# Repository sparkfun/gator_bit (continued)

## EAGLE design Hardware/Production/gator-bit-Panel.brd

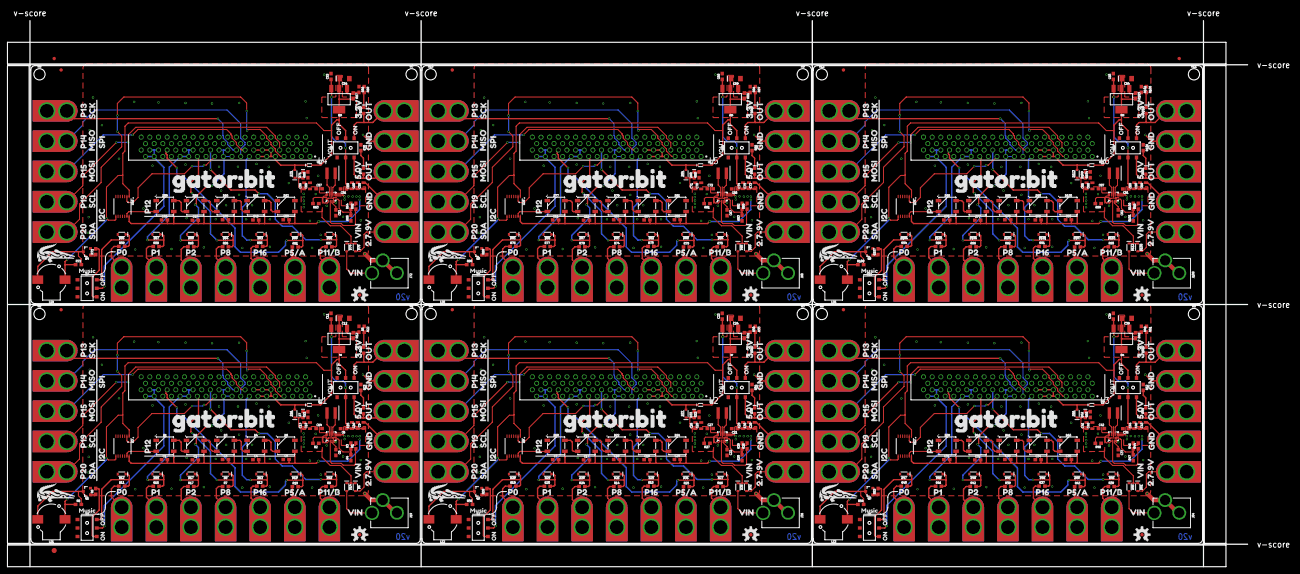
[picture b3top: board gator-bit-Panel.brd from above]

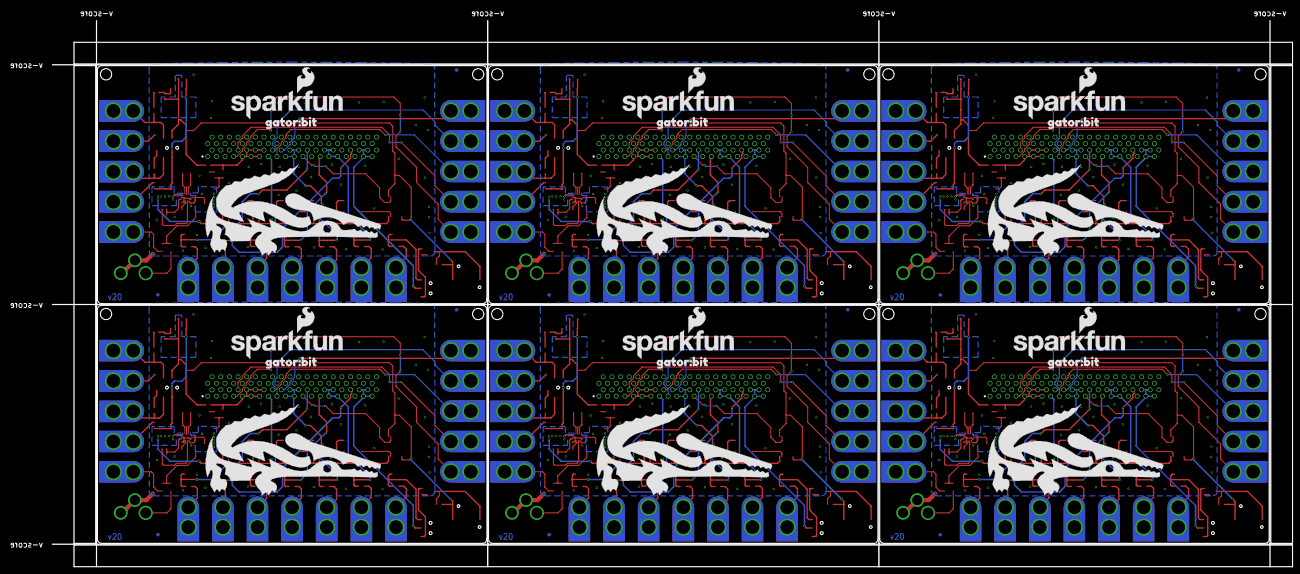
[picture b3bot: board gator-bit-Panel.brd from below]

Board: 2 copper layers, 364.0 x 160.3 mm, 765 parts (24 on the bottom side), 288 nets.

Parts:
C1, C2, C3, C4, C5, C7, C8, C11, C17, C18, C19, C20, C22, C23, C31, C32, C33, C34, C35, C37, C38, C46, C47, C48, C49, C50, C52, C53, C61, C62, C63, C64, C65, C67, C68, C76, C77, C78, C79, C80, C82, C83: 0.1uF; 0603
C6, C14, C21, C27, C36, C42, C51, C57, C66, C72, C81, C87: 10uF; 0603
C9, C15, C16, C28, C29, C30, C43, C44, C45, C58, C59, C60, C73, C74, C75, C88, C89, C90: 22uF; 0805
C10, C13, C25, C26, C40, C41, C55, C56, C70, C71, C85, C86: 10uF; 0805
C12, C24, C39, C54, C69, C84: 10uF; EIA3216
D1, D2, D3, D4, D5, D20, D21, D22, D23, D24, D39, D40, D41, D42, D43, D58, D59, D60, D61, D62, D77, D78, D79, D80, D81, D96, D97, D98, D99, D100: WS2812B
D6, D14, D16, D32, D36, D37, D51, D55, D56, D70, D74, D75, D89, D93, D94, D108, D112, D113: 1A/23V/620mV; SOD-323
D7, D9, D11, D33, D34, D35, D52, D53, D54, D71, D72, D73, D90, D91, D92, D109, D110, D111: RED; LED-0603
D8, D10, D12, D13, D15, D17, D19, D25, D26, D27, D28, D29, D30, D31, D44, D45, D46, D47, D48, D49, D50, D63, D64, D65, D66, D67, D68, D69, D82, D83, D84, D85, D86, D87, D88, D101, D102, D103, D104, D105, D106, D107: 3.6V; SOD-323
D18, D38, D57, D76, D95, D114: 120mA/40V/370mV; SOD-523
E$1, E$2: FIDUCIAL-1X2
E$3: FIDUCIAL-1.5X3
FD1, FD2, FD3, FD4, FD5, FD6, FD7, FD8, FD9, FD10, FD11, FD12, FD13, FD14, FD15, FD16, FD17, FD18, FD19, FD20, FD21, FD22, FD23, FD24: FIDUCIAL1X2; FIDUCIAL-1X2
FRAME1, FRAME2, FRAME3, FRAME4, FRAME5, FRAME6, FRAME7, FRAME8, FRAME9, FRAME10, FRAME11, FRAME12: FRAME-LETTER; CREATIVE_COMMONS
H1, H2, H3, H4, H5, H6, H7, H8, H9, H10, H11, H12: STAND-OFF
J1, J2, J3, J4, J5, J6, J7, J8, J9, J10, J11, J12, J13, J14, J15, J16, J17, J18, J20, J21, J22, J23, J24, J25, J26, J27, J28, J29, J30, J31, J32, J33, J34, J35, J37, J38, J39, J40, J41, J42, J43, J44, J45, J46, J47, J48, J49, J50, J51, J52, J53, J55, J56, J57, J58, J59, J60, J61, J62, J63, J64, J65, J66, J67, J68, J69, J70, J71, J73, J74, J75, J76, J77, J78, J79, J80, J81, J82, J83, J84, J85, J86, J87, J88, J89, J91, J92, J93, J94, J95, J96, J97, J98, J99, J100, J101, J102, J103, J104, J105, J106, J107: GATOR
J19, J36, J54, J72, J90, J108: POWER_JACKPTH_LOCK; POWER_JACK_PTH_LOCK
L1, L2, L3, L4, L5, L6: 1.5uH; XFL4020
LOGO1, LOGO4, LOGO7, LOGO10, LOGO13, LOGO16: SFE_LOGO_NAME_FLAME.3_INCH; SFE_LOGO_NAME_FLAME_.3
LOGO2, LOGO5, LOGO8, LOGO11, LOGO14, LOGO17: OSHW-LOGOM; OSHW-LOGO-M
LOGO3, LOGO6, LOGO9, LOGO12, LOGO15, LOGO18: REVISION
LS1, LS2, LS3, LS4, LS5, LS6: BUZZER-SMD; BUZZER-CCV
Q1, Q2, Q3, Q4, Q5, Q6: 600mA/40V; SOT23-3
R1, R4, R26, R29, R44, R47, R62, R65, R80, R83, R98, R101: 100k; 0603
R2, R27, R45, R63, R81, R99: 10.2K; 0603
R3, R28, R46, R64, R82, R100: 523k; 0603
R5, R30, R48, R66, R84, R102: 390; 0603
R6, R7, R9, R10, R11, R13, R14, R15, R16, R17, R18, R19, R20, R24, R25, R35, R37, R38, R39, R40, R41, R42, R43, R53, R55, R56, R57, R58, R59, R60, R61, R71, R73, R74, R75, R76, R77, R78, R79, R89, R91, R92, R93, R94, R95, R96, R97, R107: 100; 0603
R8, R36, R54, R72, R90, R108: 10k; 0603
R12, R31, R49, R67, R85, R103: 240; 0603
R21, R22, R23, R32, R33, R34, R50, R51, R52, R68, R69, R70, R86, R87, R88, R104, R105, R106: 1k; 0603
S1, S2, S3, S4, S5, S6, S7, S8, S9, S10, S11, S12: SWITCH_DPDT_SMD_AYZ0202
U1, U6, U10, U14, U18, U22: TPS63070; TPS63070RNM
U2, U5, U9, U13, U17, U21: micro:bit; MICRO:BIT_RA_PTH
U3, U8, U12, U16, U20, U24: TXB0104; TSSOP14
U4, U7, U11, U15, U19, U23: ADJ REG 1.5A; SOT223
U$1, U$4, U$75, U$112, U$149, U$186: 2#7#9V21
U$2, U$38, U$76, U$113, U$150, U$187: 3#3V25
U$3, U$40, U$77, U$114, U$151, U$188: 5#0V23
U$5, U$41, U$78, U$115, U$152, U$189: GATOR#BIT26
U$6, U$42, U$79, U$116, U$153, U$190: GATOR#BIT32
U$7, U$8, U$43, U$44, U$80, U$81, U$117, U$118, U$154, U$155, U$191, U$192: GND22
U$9, U$45, U$82, U$119, U$156, U$193: I2C7
U$10, U$46, U$83, U$120, U$157, U$194: MISO5
U$11, U$47, U$84, U$121, U$158, U$195: MOSI4
U$12, U$48, U$85, U$122, U$159, U$196: MUSIC28
U$13, U$36, U$49, U$72, U$86, U$109, U$123, U$146, U$160, U$183, U$197, U$220: OFF29
U$14, U$37, U$50, U$73, U$87, U$110, U$124, U$147, U$161, U$184, U$198, U$221: ON30
U$15, U$16, U$51, U$52, U$88, U$89, U$125, U$126, U$162, U$163, U$199, U$200: OUT24
U$17, U$53, U$90, U$127, U$164, U$201: P5#A18
U$18, U$54, U$91, U$128, U$165, U$202: P11#B19
U$19, U$55, U$92, U$129, U$166, U$203: P013
U$20, U$56, U$93, U$130, U$167, U$204: P114
U$21, U$57, U$94, U$131, U$168, U$205: P130
U$22, U$58, U$95, U$132, U$169, U$206: P199
U$23, U$59, U$96, U$133, U$170, U$207: P208
U$24, U$60, U$97, U$134, U$171, U$208: P215
U$25, U$61, U$98, U$135, U$172, U$209: P816
U$26, U$62, U$99, U$136, U$173, U$210: P1227
U$27, U$63, U$100, U$137, U$174, U$211: P1411
U$28, U$64, U$101, U$138, U$175, U$212: P1510
U$29, U$65, U$102, U$139, U$176, U$213: P1617
U$30, U$66, U$103, U$140, U$177, U$214: SCK1
U$31, U$67, U$104, U$141, U$178, U$215: SCL2
U$32, U$68, U$105, U$142, U$179, U$216: SDA3
U$33, U$69, U$106, U$143, U$180, U$217: SPI6
U$34, U$39, U$70, U$74, U$107, U$111, U$144, U$148, U$181, U$185, U$218, U$222: VIN20
U$35, U$71, U$108, U$145, U$182, U$219: VOUT31

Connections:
3.3V: C12.+, D18.A, LS1.+, R8.1, R12.2, S1.2, U3.1, U3.8, U4.2, U4.4
3.3V1: C24.+, D38.A, LS2.+, R31.2, R36.1, S4.2, U7.2, U7.4, U8.1, U8.8
3.3V2: C39.+, D57.A, LS3.+, R49.2, R54.1, S6.2, U11.2, U11.4, U12.1, U12.8
3.3V3: C54.+, D76.A, LS4.+, R67.2, R72.1, S8.2, U15.2, U15.4, U16.1, U16.8
3.3V4: C69.+, D95.A, LS5.+, R85.2, R90.1, S10.2, U19.2, U19.4, U20.1, U20.8
3.3V5: C84.+, D114.A, LS6.+, R103.2, R108.1, S12.2, U23.2, U23.4, U24.1, U24.8
5V: C1.2, C2.2, C3.2, C4.2, C5.2, C6.1, C9.1, C11.1, C15.1, C16.1, D1.1, D2.1, D3.1, D4.1, D5.1, R1.2, R3.2, S1.5, U1.P$7, U3.14, U4.3
5V1: C7.2, C17.2, C18.2, C19.2, C20.2, C21.1, C23.1, C28.1, C29.1, C30.1, D20.1, D21.1, D22.1, D23.1, D24.1, R26.2, R28.2, S4.5, U6.P$7, U7.3, U8.14
5V2: C31.2, C32.2, C33.2, C34.2, C35.2, C36.1, C38.1, C43.1, C44.1, C45.1, D39.1, D40.1, D41.1, D42.1, D43.1, R44.2, R46.2, S6.5, U10.P$7, U11.3, U12.14
5V3: C46.2, C47.2, C48.2, C49.2, C50.2, C51.1, C53.1, C58.1, C59.1, C60.1, D58.1, D59.1, D60.1, D61.1, D62.1, R62.2, R64.2, S8.5, U14.P$7, U15.3, U16.14
5V4: C61.2, C62.2, C63.2, C64.2, C65.2, C66.1, C68.1, C73.1, C74.1, C75.1, D77.1, D78.1, D79.1, D80.1, D81.1, R80.2, R82.2, S10.5, U18.P$7, U19.3, U20.14
5V5: C76.2, C77.2, C78.2, C79.2, C80.2, C81.1, C83.1, C88.1, C89.1, C90.1, D96.1, D97.1, D98.1, D99.1, D100.1, R98.2, R100.2, S12.5, U22.P$7, U23.3, U24.14
GND: C1.1, C2.1, C3.1, C4.1, C5.1, C6.2, C8.2, C9.2, C10.2, C11.2, C12.-, C13.2, C14.2, C15.2, C16.2, D1.3, D2.3, D3.3, D4.3, D5.3, D8.A, D10.A, D12.A, D13.A, D15.A, D17.A, D19.A, J2.P$1, J2.P$2, J4.P$1, J4.P$2, J19.GND, J19.GNDBREAK, Q1.2, R4.1, R5.1, R21.1, R22.1, R23.1, U1.P$4, U1.P$6, U1.P$10, U1.P$15, U2.A1, U2.A2, U2.A3, U2.A4, U2.A5, U2.A6, U3.7
GND1: C7.1, C17.1, C18.1, C19.1, C20.1, C21.2, C22.2, C23.2, C24.-, C25.2, C26.2, C27.2, C28.2, C29.2, C30.2, D20.3, D21.3, D22.3, D23.3, D24.3, D25.A, D26.A, D27.A, D28.A, D29.A, D30.A, D31.A, J32.P$1, J32.P$2, J34.P$1, J34.P$2, J36.GND, J36.GNDBREAK, Q2.2, R29.1, R30.1, R32.1, R33.1, R34.1, U5.A1, U5.A2, U5.A3, U5.A4, U5.A5, U5.A6, U6.P$4, U6.P$6, U6.P$10, U6.P$15, U8.7
GND2: C31.1, C32.1, C33.1, C34.1, C35.1, C36.2, C37.2, C38.2, C39.-, C40.2, C41.2, C42.2, C43.2, C44.2, C45.2, D39.3, D40.3, D41.3, D42.3, D43.3, D44.A, D45.A, D46.A, D47.A, D48.A, D49.A, D50.A, J50.P$1, J50.P$2, J52.P$1, J52.P$2, J54.GND, J54.GNDBREAK, Q3.2, R47.1, R48.1, R50.1, R51.1, R52.1, U9.A1, U9.A2, U9.A3, U9.A4, U9.A5, U9.A6, U10.P$4, U10.P$6, U10.P$10, U10.P$15, U12.7
GND3: C46.1, C47.1, C48.1, C49.1, C50.1, C51.2, C52.2, C53.2, C54.-, C55.2, C56.2, C57.2, C58.2, C59.2, C60.2, D58.3, D59.3, D60.3, D61.3, D62.3, D63.A, D64.A, D65.A, D66.A, D67.A, D68.A, D69.A, J68.P$1, J68.P$2, J70.P$1, J70.P$2, J72.GND, J72.GNDBREAK, Q4.2, R65.1, R66.1, R68.1, R69.1, R70.1, U13.A1, U13.A2, U13.A3, U13.A4, U13.A5, U13.A6, U14.P$4, U14.P$6, U14.P$10, U14.P$15, U16.7
GND4: C61.1, C62.1, C63.1, C64.1, C65.1, C66.2, C67.2, C68.2, C69.-, C70.2, C71.2, C72.2, C73.2, C74.2, C75.2, D77.3, D78.3, D79.3, D80.3, D81.3, D82.A, D83.A, D84.A, D85.A, D86.A, D87.A, D88.A, J86.P$1, J86.P$2, J88.P$1, J88.P$2, J90.GND, J90.GNDBREAK, Q5.2, R83.1, R84.1, R86.1, R87.1, R88.1, U17.A1, U17.A2, U17.A3, U17.A4, U17.A5, U17.A6, U18.P$4, U18.P$6, U18.P$10, U18.P$15, U20.7
GND5: C76.1, C77.1, C78.1, C79.1, C80.1, C81.2, C82.2, C83.2, C84.-, C85.2, C86.2, C87.2, C88.2, C89.2, C90.2, D96.3, D97.3, D98.3, D99.3, D100.3, D101.A, D102.A, D103.A, D104.A, D105.A, D106.A, D107.A, J104.P$1, J104.P$2, J106.P$1, J106.P$2, J108.GND, J108.GNDBREAK, Q6.2, R101.1, R102.1, R104.1, R105.1, R106.1, U21.A1, U21.A2, U21.A3, U21.A4, U21.A5, U21.A6, U22.P$4, U22.P$6, U22.P$10, U22.P$15, U24.7
MBIN: D16.A, D18.C, U2.A9, U2.A10, U2.A11, U2.A12, U2.A13, U2.A14
MBIN1: D37.A, D38.C, U5.A9, U5.A10, U5.A11, U5.A12, U5.A13, U5.A14
MBIN2: D56.A, D57.C, U9.A9, U9.A10, U9.A11, U9.A12, U9.A13, U9.A14
MBIN3: D75.A, D76.C, U13.A9, U13.A10, U13.A11, U13.A12, U13.A13, U13.A14
MBIN4: D94.A, D95.C, U17.A9, U17.A10, U17.A11, U17.A12, U17.A13, U17.A14
MBIN5: D113.A, D114.C, U21.A9, U21.A10, U21.A11, U21.A12, U21.A13, U21.A14
unnamed: D20.2, D21.4
unnamed: L1.P$1, U1.P$11
unnamed: LS1.-, Q1.3, R8.2
unnamed: D1.2, D2.4
unnamed: D2.2, D3.4
unnamed: D3.2, D4.4
unnamed: D4.2, D5.4
unnamed: L1.P$2, U1.P$9
unnamed: D7.C, R21.2
unnamed: D21.2, D22.4
unnamed: R3.1, R4.2, U1.P$5
unnamed: C8.1, U1.P$3
unnamed: R2.2, U1.P$1, U1.P$14
unnamed: R1.1, U1.P$2
unnamed: D22.2, D23.4
unnamed: R5.2, R12.1, U4.1
unnamed: D23.2, D24.4
unnamed: L2.P$1, U6.P$11
unnamed: L2.P$2, U6.P$9
unnamed: R6.2, S3.3
unnamed: R27.2, U6.P$1, U6.P$14
unnamed: D9.C, R22.2
unnamed: D11.C, R23.2
unnamed: Q1.1, R6.1
unnamed: C22.1, U6.P$3
unnamed: R28.1, R29.2, U6.P$5
unnamed: R26.1, U6.P$2
unnamed: R30.2, R31.1, U7.1
unnamed: D33.C, R32.2
unnamed: D34.C, R33.2
unnamed: D35.C, R34.2
unnamed: R35.2, S2.3
unnamed: Q2.1, R35.1
unnamed: LS2.-, Q2.3, R36.2
unnamed: D39.2, D40.4
unnamed: D40.2, D41.4
unnamed: D41.2, D42.4
unnamed: D42.2, D43.4
unnamed: L3.P$1, U10.P$11
unnamed: L3.P$2, U10.P$9
unnamed: R45.2, U10.P$1, U10.P$14
unnamed: C37.1, U10.P$3
unnamed: R46.1, R47.2, U10.P$5
unnamed: R44.1, U10.P$2
unnamed: R48.2, R49.1, U11.1
unnamed: D52.C, R50.2
unnamed: D53.C, R51.2
unnamed: D54.C, R52.2
unnamed: R53.2, S5.3
unnamed: Q3.1, R53.1
unnamed: LS3.-, Q3.3, R54.2
unnamed: D58.2, D59.4
unnamed: D59.2, D60.4
unnamed: D60.2, D61.4
unnamed: D61.2, D62.4
unnamed: L4.P$1, U14.P$11
unnamed: L4.P$2, U14.P$9
unnamed: R63.2, U14.P$1, U14.P$14
unnamed: C52.1, U14.P$3
unnamed: R64.1, R65.2, U14.P$5
unnamed: R62.1, U14.P$2
unnamed: R66.2, R67.1, U15.1
unnamed: D71.C, R68.2
unnamed: D72.C, R69.2
unnamed: D73.C, R70.2
unnamed: R71.2, S7.3
unnamed: Q4.1, R71.1
unnamed: LS4.-, Q4.3, R72.2
unnamed: D77.2, D78.4
unnamed: D78.2, D79.4
unnamed: D79.2, D80.4
unnamed: D80.2, D81.4
unnamed: L5.P$1, U18.P$11
unnamed: L5.P$2, U18.P$9
unnamed: R81.2, U18.P$1, U18.P$14
unnamed: C67.1, U18.P$3
unnamed: R82.1, R83.2, U18.P$5
unnamed: R80.1, U18.P$2
unnamed: R84.2, R85.1, U19.1
unnamed: D90.C, R86.2
unnamed: D91.C, R87.2
unnamed: D92.C, R88.2
unnamed: R89.2, S9.3
unnamed: Q5.1, R89.1
unnamed: LS5.-, Q5.3, R90.2
unnamed: D96.2, D97.4
unnamed: D97.2, D98.4
unnamed: D98.2, D99.4
unnamed: D99.2, D100.4
unnamed: L6.P$1, U22.P$11
unnamed: L6.P$2, U22.P$9
unnamed: R99.2, U22.P$1, U22.P$14
unnamed: C82.1, U22.P$3
unnamed: R100.1, R101.2, U22.P$5
unnamed: R98.1, U22.P$2
unnamed: R102.2, R103.1, U23.1
unnamed: D109.C, R104.2
unnamed: D110.C, R105.2
unnamed: D111.C, R106.2
unnamed: R107.2, S11.3
unnamed: Q6.1, R107.1
unnamed: LS6.-, Q6.3, R108.2
P0: S3.2, U2.A36, U2.A37, U2.A38, U2.A39
P0+: J7.P$1, J7.P$2, R11.1
P0+1: J20.P$1, J20.P$2, R18.1
P0+2: J38.P$1, J38.P$2, R40.1
P0+3: J56.P$1, J56.P$2, R58.1
P0+4: J74.P$1, J74.P$2, R76.1
P0+5: J92.P$1, J92.P$2, R94.1
P1: D15.C, R15.2, U2.A28, U2.A29, U2.A30, U2.A31
P1+: J8.P$1, J8.P$2, R15.1
P1+1: J21.P$1, J21.P$2, R20.1
P1+2: J39.P$1, J39.P$2, R41.1
P1+3: J57.P$1, J57.P$2, R59.1
P1+4: J75.P$1, J75.P$2, R77.1
P1+5: J93.P$1, J93.P$2, R95.1
P2: D17.C, R17.2, U2.A19, U2.A20, U2.A21, U2.A22
P2+: J9.P$1, J9.P$2, R17.1
P2+1: J22.P$1, J22.P$2, R24.1
P2+2: J40.P$1, J40.P$2, R42.1
P2+3: J58.P$1, J58.P$2, R60.1
P2+4: J76.P$1, J76.P$2, R78.1
P2+5: J94.P$1, J94.P$2, R96.1
P3: D27.C, R16.2, U5.A24
P4: D31.C, R25.2, U5.A34
P5: D19.C, R19.2, U2.A34
P5+: J10.P$1, J10.P$2, R19.1
P5+1: J23.P$1, J23.P$2, R25.1
P5+2: J41.P$1, J41.P$2, R43.1
P5+3: J59.P$1, J59.P$2, R61.1
P5+4: J77.P$1, J77.P$2, R79.1
P5+5: J95.P$1, J95.P$2, R97.1
P6: S2.2, U5.A36, U5.A37, U5.A38, U5.A39
P7: D29.C, R20.2, U5.A28, U5.A29, U5.A30, U5.A31
P8: D8.C, R7.2, U2.A27
P8+: J11.P$1, J11.P$2, R7.1
P8+1: J24.P$1, J24.P$2, R14.1
P8+2: J42.P$1, J42.P$2, R38.1
P8+3: J60.P$1, J60.P$2, R56.1
P8+4: J78.P$1, J78.P$2, R74.1
P8+5: J96.P$1, J96.P$2, R92.1
P9: D26.C, R14.2, U5.A27
P10: D20.4, U8.13
P11: D10.C, R9.2, U2.A24
P11+: J18.P$1, J18.P$2, R9.1
P11+1: J31.P$1, J31.P$2, R16.1
P11+2: J49.P$1, J49.P$2, R39.1
P11+3: J67.P$1, J67.P$2, R57.1
P11+4: J85.P$1, J85.P$2, R75.1
P11+5: J103.P$1, J103.P$2, R93.1
P12: D1.4, U3.13
P12LL: U2.A23, U3.2
P12LL1: U5.A23, U8.2
P12LL2: U9.A23, U12.2
P12LL3: U13.A23, U16.2
P12LL4: U17.A23, U20.2
P12LL5: U21.A23, U24.2
P13: J12.P$1, J12.P$2, U2.A18
P14: J13.P$1, J13.P$2, U2.A17
P15: J14.P$1, J14.P$2, U2.A16
P16: D13.C, R13.2, U2.A15
P16+: J15.P$1, J15.P$2, R13.1
P16+1: J28.P$1, J28.P$2, R10.1
P16+2: J46.P$1, J46.P$2, R37.1
P16+3: J64.P$1, J64.P$2, R55.1
P16+4: J82.P$1, J82.P$2, R73.1
P16+5: J100.P$1, J100.P$2, R91.1
P17: D30.C, R24.2, U5.A19, U5.A20, U5.A21, U5.A22
P18: J25.P$1, J25.P$2, U5.A18
P19: J16.P$1, J16.P$2, U2.A8
P20: J17.P$1, J17.P$2, U2.A7
P21: J26.P$1, J26.P$2, U5.A17
P22: J27.P$1, J27.P$2, U5.A16
P23: D25.C, R10.2, U5.A15
P24: J29.P$1, J29.P$2, U5.A8
P25: J30.P$1, J30.P$2, U5.A7
P26: D46.C, R39.2, U9.A24
P27: D50.C, R43.2, U9.A34
P28: S5.2, U9.A36, U9.A37, U9.A38, U9.A39
P29: D48.C, R41.2, U9.A28, U9.A29, U9.A30, U9.A31
P30: D45.C, R38.2, U9.A27
P31: D39.4, U12.13
P32: D49.C, R42.2, U9.A19, U9.A20, U9.A21, U9.A22
P33: J43.P$1, J43.P$2, U9.A18
P34: J44.P$1, J44.P$2, U9.A17
P35: J45.P$1, J45.P$2, U9.A16
P36: D44.C, R37.2, U9.A15
P37: J47.P$1, J47.P$2, U9.A8
P38: J48.P$1, J48.P$2, U9.A7
P39: D65.C, R57.2, U13.A24
P40: D69.C, R61.2, U13.A34
P41: S7.2, U13.A36, U13.A37, U13.A38, U13.A39
P42: D67.C, R59.2, U13.A28, U13.A29, U13.A30, U13.A31
P43: D64.C, R56.2, U13.A27
P44: D58.4, U16.13
P45: D68.C, R60.2, U13.A19, U13.A20, U13.A21, U13.A22
P46: J61.P$1, J61.P$2, U13.A18
P47: J62.P$1, J62.P$2, U13.A17
P48: J63.P$1, J63.P$2, U13.A16
P49: D63.C, R55.2, U13.A15
P50: J65.P$1, J65.P$2, U13.A8
P51: J66.P$1, J66.P$2, U13.A7
P52: D84.C, R75.2, U17.A24
P53: D88.C, R79.2, U17.A34
P54: S9.2, U17.A36, U17.A37, U17.A38, U17.A39
P55: D86.C, R77.2, U17.A28, U17.A29, U17.A30, U17.A31
P56: D83.C, R74.2, U17.A27
P57: D77.4, U20.13
P58: D87.C, R78.2, U17.A19, U17.A20, U17.A21, U17.A22
P59: J79.P$1, J79.P$2, U17.A18
P60: J80.P$1, J80.P$2, U17.A17
P61: J81.P$1, J81.P$2, U17.A16
P62: D82.C, R73.2, U17.A15
P63: J83.P$1, J83.P$2, U17.A8
P64: J84.P$1, J84.P$2, U17.A7
P65: D103.C, R93.2, U21.A24
P66: D107.C, R97.2, U21.A34
P67: S11.2, U21.A36, U21.A37, U21.A38, U21.A39
P68: D105.C, R95.2, U21.A28, U21.A29, U21.A30, U21.A31
P69: D102.C, R92.2, U21.A27
P70: D96.4, U24.13
P71: D106.C, R96.2, U21.A19, U21.A20, U21.A21, U21.A22
P72: J97.P$1, J97.P$2, U21.A18
P73: J98.P$1, J98.P$2, U21.A17
P74: J99.P$1, J99.P$2, U21.A16
P75: D101.C, R91.2, U21.A15
P76: J101.P$1, J101.P$2, U21.A8
P77: J102.P$1, J102.P$2, U21.A7
PD: D12.C, R11.2, S3.1
PD1: D28.C, R18.2, S2.1
PD2: D47.C, R40.2, S5.1
PD3: D66.C, R58.2, S7.1
PD4: D85.C, R76.2, S9.1
PD5: D104.C, R94.2, S11.1
VIN: C10.1, C13.1, C14.1, D6.C, D7.A, D14.C, D16.C, R2.1, U1.P$12
VIN1: C25.1, C26.1, C27.1, D32.C, D33.A, D36.C, D37.C, R27.1, U6.P$12
VIN2: C40.1, C41.1, C42.1, D51.C, D52.A, D55.C, D56.C, R45.1, U10.P$12
VIN3: C55.1, C56.1, C57.1, D70.C, D71.A, D74.C, D75.C, R63.1, U14.P$12
VIN4: C70.1, C71.1, C72.1, D89.C, D90.A, D93.C, D94.C, R81.1, U18.P$12
VIN5: C85.1, C86.1, C87.1, D108.C, D109.A, D112.C, D113.C, R99.1, U22.P$12
VIN_TAB: D6.A, J3.P$1, J3.P$2
VIN_TAB1: D32.A, J33.P$1, J33.P$2
VIN_TAB2: D51.A, J51.P$1, J51.P$2
VIN_TAB3: D70.A, J69.P$1, J69.P$2
VIN_TAB4: D89.A, J87.P$1, J87.P$2
VIN_TAB5: D108.A, J105.P$1, J105.P$2
VOUT3.1: D34.A, J5.P$1, J5.P$2, S4.3
VOUT3.2: D53.A, J37.P$1, J37.P$2, S6.3
VOUT3.3: D9.A, J6.P$1, J6.P$2, S1.3
VOUT3.4: D72.A, J55.P$1, J55.P$2, S8.3
VOUT3.5: D91.A, J73.P$1, J73.P$2, S10.3
VOUT3.6: D110.A, J91.P$1, J91.P$2, S12.3
VOUT5.0: D11.A, J1.P$1, J1.P$2, S1.6
VOUT5.1: D35.A, J35.P$1, J35.P$2, S4.6
VOUT5.2: D54.A, J53.P$1, J53.P$2, S6.6
VOUT5.3: D73.A, J71.P$1, J71.P$2, S8.6
VOUT5.4: D92.A, J89.P$1, J89.P$2, S10.6
VOUT5.5: D111.A, J107.P$1, J107.P$2, S12.6
V_BATT: D14.A, J19.PWR
V_BATT1: D36.A, J36.PWR
V_BATT2: D55.A, J54.PWR
V_BATT3: D74.A, J72.PWR
V_BATT4: D93.A, J90.PWR
V_BATT5: D112.A, J108.PWR

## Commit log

2017-09-15 Pulling board file from personal repo
2017-09-15 Updated Board File Silk
2017-09-18 Updating BRD and SCH files -fixed switch problem - isolate speaker and protected pin 0 line -Added silk labels to GPIO -Aesthetics on SCH
2017-09-18 Updated SILK on BRD file
2017-09-20 Added a battery connector
2017-09-21 Add JST battery connector
2017-09-26 Updated design
2017-09-26 adding bstop
2017-09-26 adding OSHW logo, VIN range note
2017-09-26 updating resistor values
2017-10-16 Updating file
2017-10-24 Updating Design Files
2017-10-27 updating brd file
2017-10-27 Added Inductor
2017-10-31 Updated Brd and Sch files
2017-11-03 added SOT223 package for 3.3V regulated output
2017-11-03 added holes for lego compatibility
2017-11-03 decreased size of 3.3V polygon pour
2017-11-06 Fixing traces
2017-11-06 Updated parts with SKUs
2017-11-06 updating Buck-Boost part
2017-11-06 Fixing ground pour
2017-11-08 Updates Per QC Review
2017-11-08 fixing 604 Resistor Package
2017-11-08 Updating VREG 3.0V Package
2018-01-24 -Updated protection diodes -added a power path to be powered from the micro:bit -added master switch -added status LEDs
2018-01-26 -Added Fuse to 3.3V input on the m:b -added silk to show users the sequence of switches -added option to choose powering from m:b (USB) or from an external power supply.
2018-01-29 v02, silk
2018-01-29 added logos
2018-01-30 Updating per QC Review
2018-01-31 Updating TXB package
2018-02-02 prop to vect text
2018-02-26 Updated TXB0104PWR package
2018-03-21 updating Silk Logo
2018-03-23 updated version number
2018-03-23 updated per QC review
2018-03-28 created panel v10
2018-04-26 Updating inductor package
2018-05-07 Updating ReadMe with applicable links
    Updating ReadMe with applicable links
2018-12-19 initial commit to v20
2018-12-20 updating schematic to include revised by on second sheet
2018-12-20 Post checklist changes
2019-01-08 gator:bit Example Code HEX files
    Add compiled MakeCode example code used in with gator:bit
2019-01-10 post review/checklist changes
2019-01-11 repositioning schematic text, qc double check changes
2019-01-21 panel
2019-01-30 updating readme
2019-10-08 Update Versions
2019-10-08 Update for Archiving
    Added retired notification
2019-10-08 Update Link
2019-10-08 Update Link and Comment
2022-04-01 Power diodes updated
    * D6, D14, D16 schottky diodes replaced with DIO-14072 which has a 280 mV forward voltage. Sparkle BOM updated as well.
